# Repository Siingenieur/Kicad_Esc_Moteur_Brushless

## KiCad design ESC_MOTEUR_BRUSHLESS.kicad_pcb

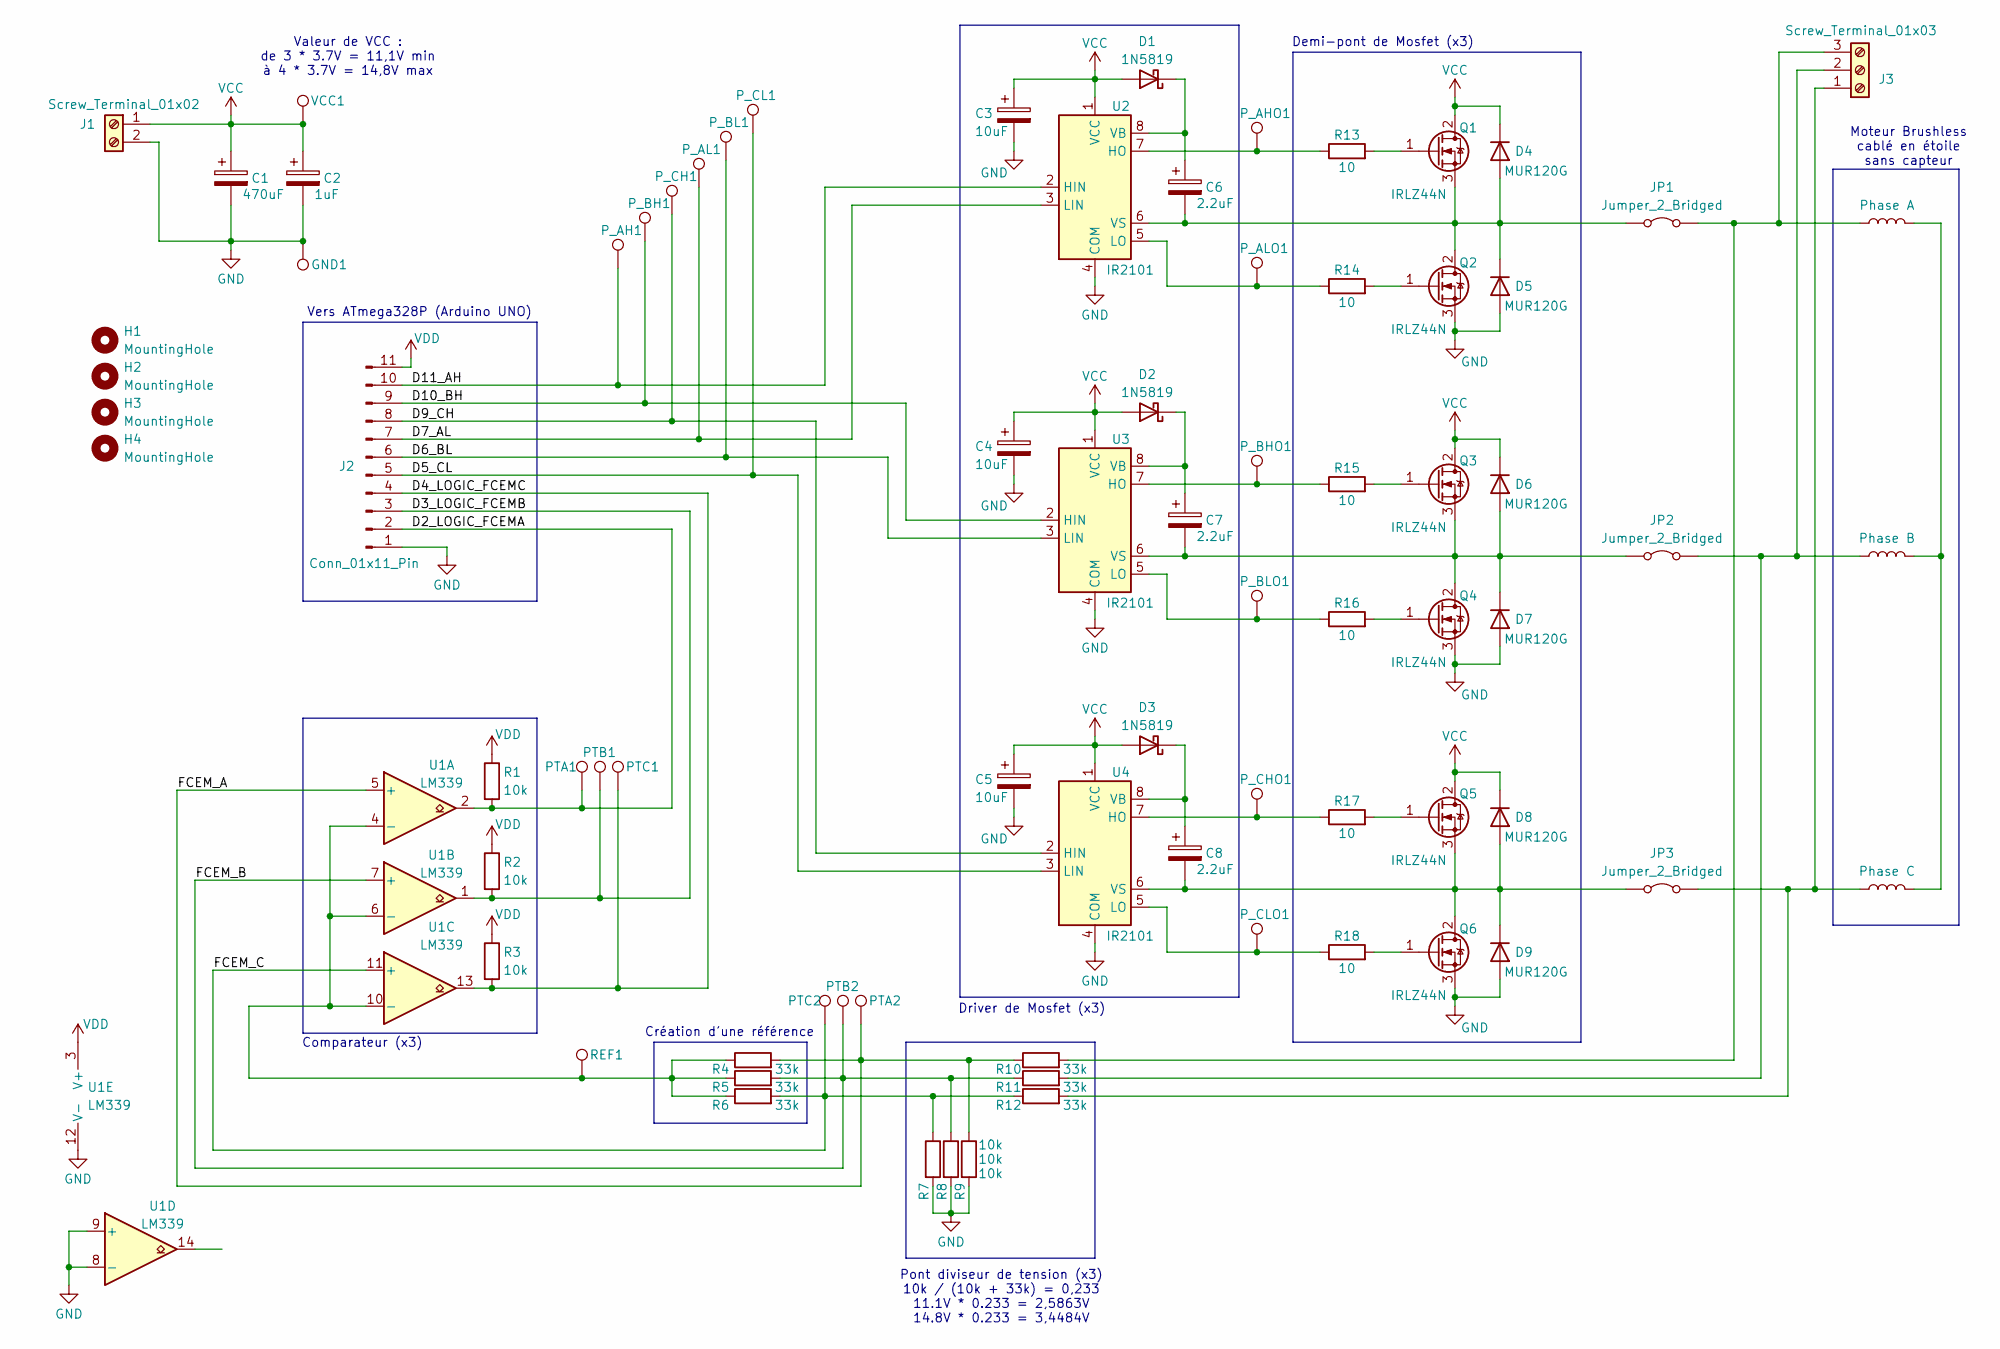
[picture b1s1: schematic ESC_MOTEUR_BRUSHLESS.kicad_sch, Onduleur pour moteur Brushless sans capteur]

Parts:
C1: 470uF; CP_Radial_D8.0mm_P5.00mm
C2: 1uF; CP_Radial_D8.0mm_P5.00mm
C3, C4, C5: 10uF; CP_Radial_D5.0mm_P2.00mm
C6, C7, C8: 2.2uF; CP_Radial_D5.0mm_P2.00mm
D1, D2, D3: 1N5819; D_DO-41_SOD81_P10.16mm_Horizontal
D4, D5, D6, D7, D8, D9: MUR120G; D_DO-41_SOD81_P10.16mm_Horizontal
GND1: TestPoint; TestPoint_THTPad_D1.5mm_Drill0.7mm
H1, H2, H3, H4: MountingHole; MountingHole_3.2mm_M3
J1: Screw_Terminal_01x02; TerminalBlock_Phoenix_MKDS-1,5-2-5.08_1x02_P5.08mm_Horizont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
J2: Conn_01x11_Pin; PinHeader_1x11_P2.54mm_Vertical
J3: Screw_Terminal_01x03; TerminalBlock_Phoenix_MKDS-1,5-3-5.08_1x03_P5.08mm_Horizont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
JP1, JP2, JP3: Jumper_2_Bridged; PinHeader_1x02_P2.54mm_Vertical
L1: Phase A
L2: Phase B
L3: Phase C
PTA1, PTA2: TestPoint; TestPoint_THTPad_D1.5mm_Drill0.7mm
PTB1, PTB2: TestPoint; TestPoint_THTPad_D1.5mm_Drill0.7mm
PTC1, PTC2: TestPoint; TestPoint_THTPad_D1.5mm_Drill0.7mm
P_AH1: TestPoint; TestPoint_THTPad_D1.5mm_Drill0.7mm
P_AHO1: TestPoint; TestPoint_THTPad_D1.5mm_Drill0.7mm
P_AL1: TestPoint; TestPoint_THTPad_D1.5mm_Drill0.7mm
P_ALO1: TestPoint; TestPoint_THTPad_D1.5mm_Drill0.7mm
P_BH1: TestPoint; TestPoint_THTPad_D1.5mm_Drill0.7mm
P_BHO1: TestPoint; TestPoint_THTPad_D1.5mm_Drill0.7mm
P_BL1: TestPoint; TestPoint_THTPad_D1.5mm_Drill0.7mm
P_BLO1: TestPoint; TestPoint_THTPad_D1.5mm_Drill0.7mm
P_CH1: TestPoint; TestPoint_THTPad_D1.5mm_Drill0.7mm
P_CHO1: TestPoint; TestPoint_THTPad_D1.5mm_Drill0.7mm
P_CL1: TestPoint; TestPoint_THTPad_D1.5mm_Drill0.7mm
P_CLO1: TestPoint; TestPoint_THTPad_D1.5mm_Drill0.7mm
Q1, Q2, Q3, Q4, Q5, Q6: IRLZ44N; TO-220-3_Vertical
R1, R2, R3, R7, R8, R9: 10k; R_Axial_DIN0204_L3.6mm_D1.6mm_P7.62mm_Horizontal
R4, R5, R6, R10, R11, R12: 33k; R_Axial_DIN0204_L3.6mm_D1.6mm_P7.62mm_Horizontal
R13, R14, R15, R16, R17, R18: 10; R_Axial_DIN0204_L3.6mm_D1.6mm_P7.62mm_Horizontal
REF1: TestPoint; TestPoint_THTPad_D1.5mm_Drill0.7mm
U1: LM339; DIP-14_W7.62mm
U2, U3, U4: IR2101; DIP-8_W7.62mm
VCC1: TestPoint; TestPoint_THTPad_D1.5mm_Drill0.7mm

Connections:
/D2_LOGIC_FCEMA: J2.2, PTA1.1, R1.2, U1.2
/D3_LOGIC_FCEMB: J2.3, PTB1.1, R2.2, U1.1
/D4_LOGIC_FCEMC: J2.4, PTC1.1, R3.2, U1.13
/D5_CL: J2.5, P_CL1.1, U4.3 (LIN)
/D6_BL: J2.6, P_BL1.1, U3.3 (LIN)
/D7_AL: J2.7, P_AL1.1, U2.3 (LIN)
/D9_CH: J2.8, P_CH1.1, U4.2 (HIN)
/D10_BH: J2.9, P_BH1.1, U3.2 (HIN)
/D11_AH: J2.10, P_AH1.1, U2.2 (HIN)
/FCEM_A: PTA2.1, R4.2, R9.1, R10.1, U1.5 (+)
/FCEM_B: PTB2.1, R5.2, R8.1, R11.1, U1.7 (+)
/FCEM_C: PTC2.1, R6.2, R7.1, R12.1, U1.11 (+)
GND: C1.2, C2.2, C3.2, C4.2, C5.2, D5.2 (A), D7.2 (A), D9.2 (A), GND1.1, J1.2, J2.1, Q2.3 (S), Q4.3 (S), Q6.3 (S), R7.2, R8.2, R9.2, U1.8 (-), U1.9 (+), U1.12 (V-), U2.4 (COM), U3.4 (COM), U4.4 (COM)
unnamed: C6.1, D1.1 (K), U2.8 (VB)
unnamed: C7.1, D2.1 (K), U3.8 (VB)
unnamed: C8.1, D3.1 (K), U4.8 (VB)
unnamed: C6.2, D4.2 (A), D5.1 (K), JP1.1 (A), Q1.3 (S), Q2.2 (D), U2.6 (VS)
unnamed: C7.2, D6.2 (A), D7.1 (K), JP2.1 (A), Q3.3 (S), Q4.2 (D), U3.6 (VS)
unnamed: C8.2, D8.2 (A), D9.1 (K), JP3.1 (A), Q5.3 (S), Q6.2 (D), U4.6 (VS)
unnamed: J3.1, JP3.2 (B), L3.1, R12.2
unnamed: J3.2, JP2.2 (B), L2.1, R11.2
unnamed: J3.3, JP1.2 (B), L1.1, R10.2
unnamed: L1.2, L2.2, L3.2
unnamed: Q1.1 (G), R13.2
unnamed: Q2.1 (G), R14.2
unnamed: Q3.1 (G), R15.2
unnamed: Q4.1 (G), R16.2
unnamed: Q5.1 (G), R17.2
unnamed: Q6.1 (G), R18.2
unnamed: R4.1, R5.1, R6.1, REF1.1, U1.4 (-), U1.6 (-), U1.10 (-)
unnamed: P_AHO1.1, R13.1, U2.7 (HO)
unnamed: P_ALO1.1, R14.1, U2.5 (LO)
unnamed: P_BHO1.1, R15.1, U3.7 (HO)
unnamed: P_BLO1.1, R16.1, U3.5 (LO)
unnamed: P_CHO1.1, R17.1, U4.7 (HO)
unnamed: P_CLO1.1, R18.1, U4.5 (LO)
VCC: C1.1, C2.1, C3.1, C4.1, C5.1, D1.2 (A), D2.2 (A), D3.2 (A), D4.1 (K), D6.1 (K), D8.1 (K), J1.1, Q1.2 (D), Q3.2 (D), Q5.2 (D), U2.1 (VCC), U3.1 (VCC), U4.1 (VCC), VCC1.1
VDD: J2.11, R1.1, R2.1, R3.1, U1.3 (V+)

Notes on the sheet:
Comparateur (x3)
Pont diviseur de tension (x3) 10k / (10k + 33k) = 0,233 11.1V * 0.233 = 2,5863V 14.8V * 0.233 = 3,4484V
Création d'une référence
Valeur de VCC : de 3 * 3.7V = 11,1V min à 4 * 3.7V = 14,8V max
Demi-pont de Mosfet (x3)
Moteur Brushless cablé en étoile sans capteur
Vers ATmega328P (Arduino UNO)
Driver de Mosfet (x3)

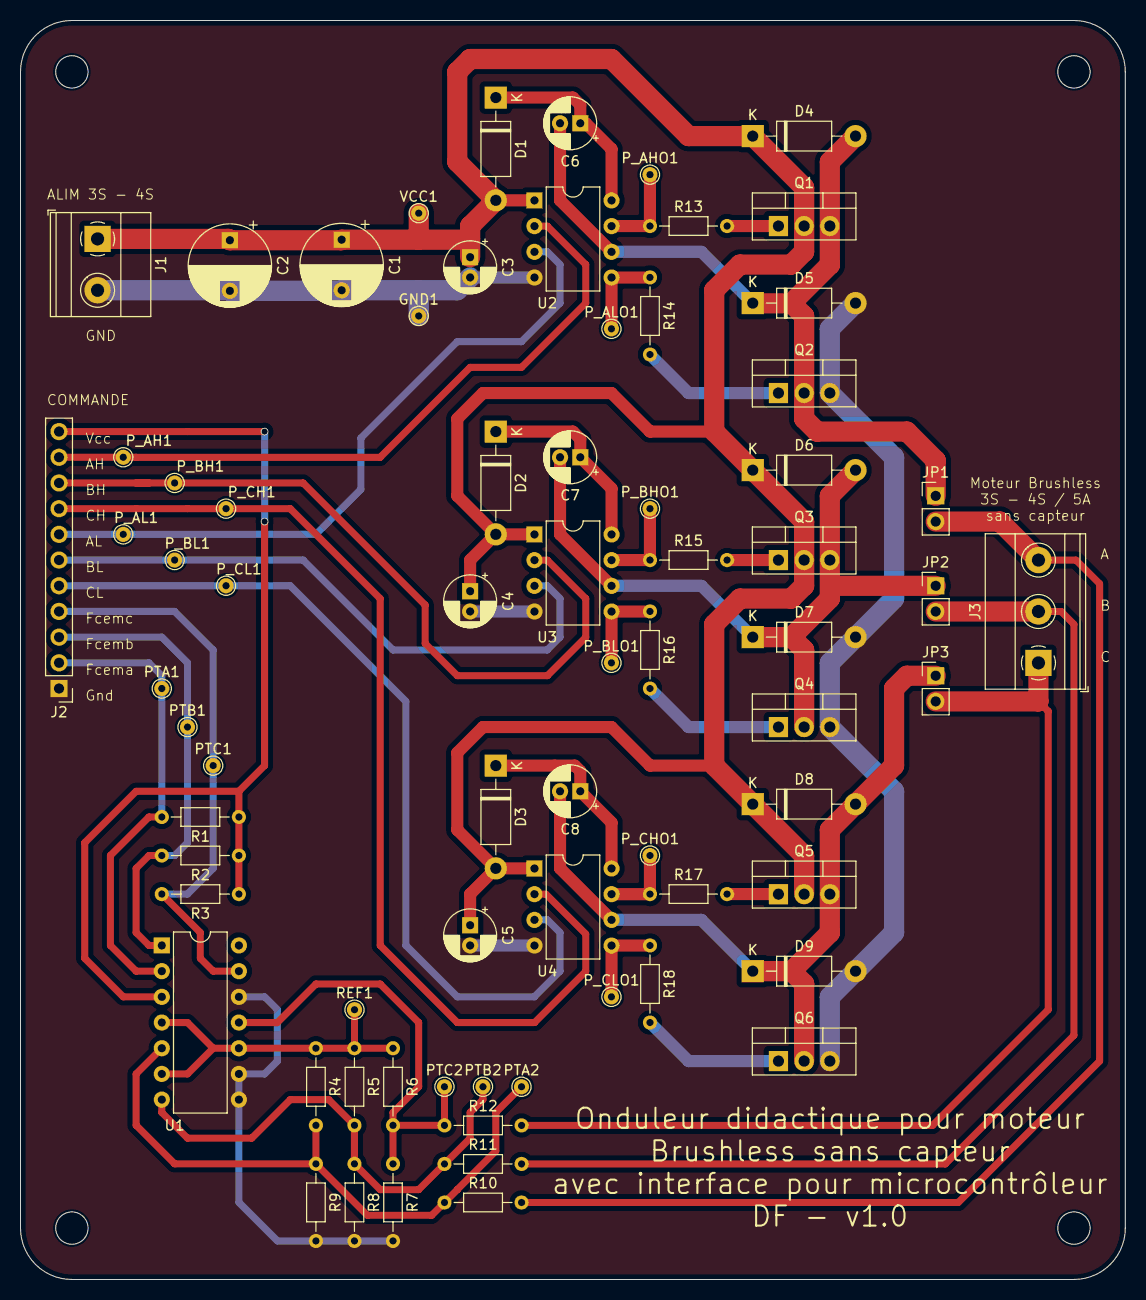
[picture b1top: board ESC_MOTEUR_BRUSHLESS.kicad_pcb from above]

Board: 2 copper layers, 109.2 x 124.5 mm, 76 parts (0 on the bottom side), 37 nets.

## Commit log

2024-10-07 init
2024-10-07 mise à jour
2024-10-10 version finale 1.1
